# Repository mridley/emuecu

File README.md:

# emuecu
Emu ECU - An ECU for flightless birds

An ECU for UAV applications

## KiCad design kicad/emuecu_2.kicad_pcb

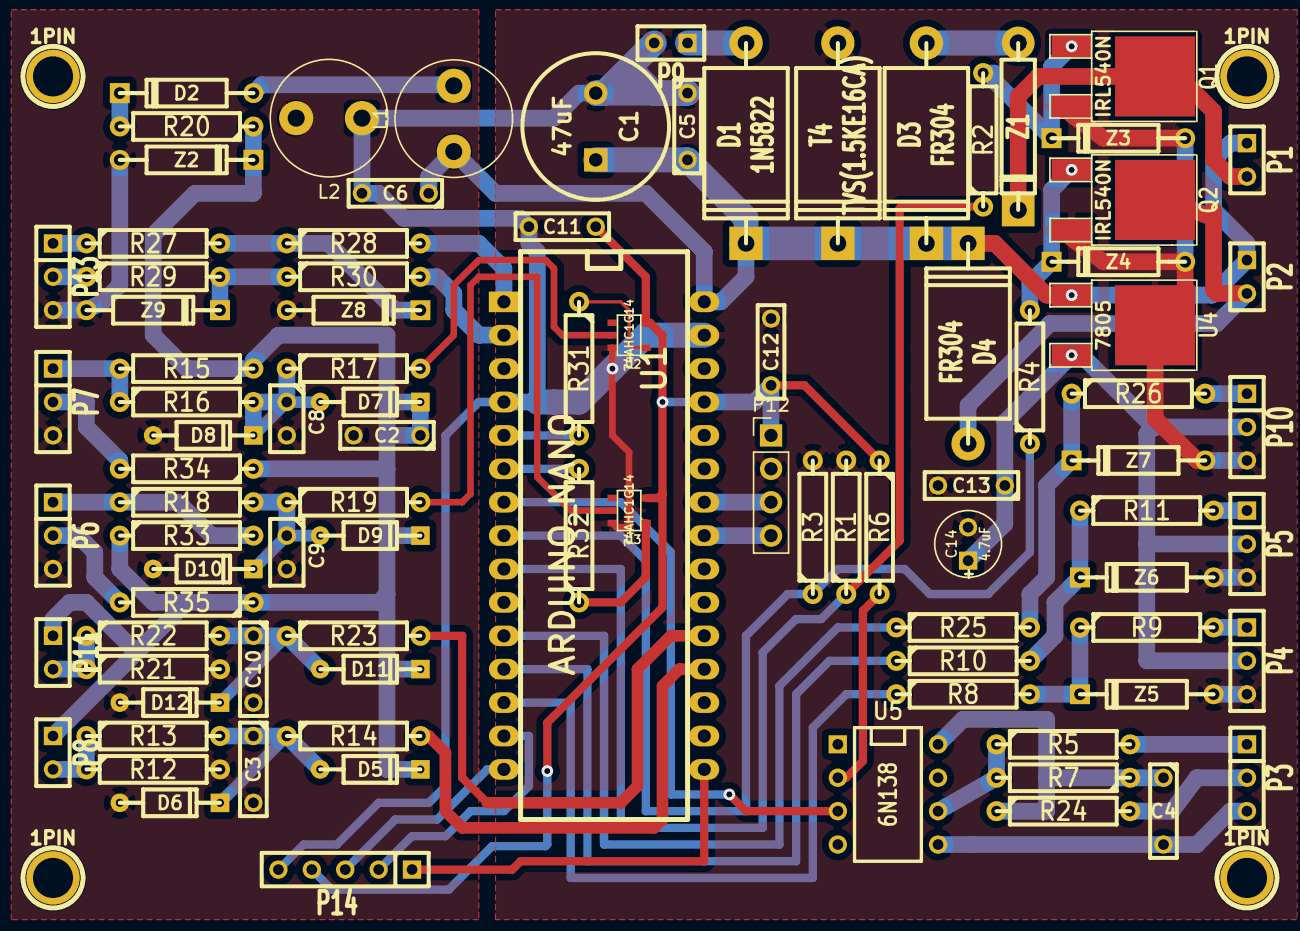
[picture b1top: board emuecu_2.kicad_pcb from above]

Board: 2 copper layers, 97 parts (0 on the bottom side), 61 nets.

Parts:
1PIN, 1PIN#2, 1PIN#3, 1PIN#4: P***; 1pin
C1: 47uF; C2V10
C2: 0.1 uF; C2
C3, C4, C5, C6, C10, C11, C12, C13: 0.1uF; C2
C8, C9: 10pF; C1
C14: 4.7uF; C1V5
D1: 1N5822; D6
D2: 1N4002; DO-41
D3, D4: FR304; D6
D5, D6, D7, D8, D9, D10, D11, D12: BAT48; DO-35
L1, L2: 47uH; L_Radial_D8.7mm_P5.00mm_Fastron_07HCP
P1: INJECTOR; SIL-2
P2: FAN/PUMP; SIL-2
P3: IGNITION; SIL-3
P4: LOAD; SIL-3
P5: THROTTLE; SIL-3
P6: SERVO; SIL-3
P7: HALL; SIL-3
P8: ENG TEMP; SIL-2
P9: POWER; SIL-2
P10: PUMP; SIL-3
P11: AIR TEMP; SIL-2
P12: I2C; PinHeader_1x04_P2.54mm_Vertical
P13: Serial; SIL-3
P14: SPI; SIL-5
Q1, Q2: IRL540N; DPAK2
R1, R3: 47k; R4
R2, R4, R14, R17, R19, R23, R30: 1k; R4
R5: 200; R4
R6: 330; R4
R7: 2.2k; R4
R8, R10, R25, R28, R31, R32: 180; R4
R9, R11, R26, R27: 470; R4
R12, R21: 22k; R4
R13, R15, R16, R18, R22, R29, R33: 10k; R4
R20: 240; R4
R24: 220; R4
R34, R35: 100; R4
T4: TVS(1.5KE16CA); D6
U1: ARDUINO_NANO; arduino_nano
U2, U3: 74AHC1G14; SOT23-5
U4: 7805; DPAK2
U5: 6N138; DIP-8__300
Z1: 1N5365B; D5
Z2: IN5919BG (5.6V); DO-41
Z3, Z4, Z5, Z6, Z7, Z8, Z9: 1N4733; DO-41

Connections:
+5C: C2.1, D5.2, D7.2, D9.2, D11.2, P8.1, P11.1, R15.1, R20.1, R33.1, R34.1, R35.1, Z2.2
+5V: C11.1, C12.1, P12.1, P14.4, R6.1, U1.27, U2.5, U3.5
+12V: C1.1, C5.1, C6.1, D1.2, D3.2, D4.2, L1.1, P1.1, P2.1, T4.2, U1.30, U4.1
GND: C1.2, C5.2, C6.2, C11.2, C12.2, C13.2, C14.2, L2.1, P4.3, P5.3, P9.2, P10.3, P12.2, P14.5, Q1.3, Q2.3, R1.2, R3.2, T4.1, U1.4, U1.29, U2.3, U3.3, U4.2, Z3.1, Z4.1, Z5.1, Z6.1, Z7.1
unnamed: C3.1, D5.1, D6.2, R13.2, R14.1
unnamed: C4.1, R7.1, R24.1, U5.8
unnamed: C4.2, P3.3, U5.5
unnamed: C8.1, D7.1, D8.2, R16.2, R17.1
unnamed: C9.1, D9.1, D10.2, R18.2, R19.1
unnamed: C10.1, D11.1, D12.2, R22.2, R23.1
unnamed: C13.1, C14.1, P4.2, P5.2, P10.2, U4.3
unnamed: D1.1, P9.1
unnamed: D2.1, L1.2
unnamed: D2.2, R20.2
unnamed: D3.1, Z1.1
unnamed: D4.1, P2.2, Q2.2
unnamed: P1.2, Q1.2, Z1.2
unnamed: P3.1, R5.2
unnamed: P3.2, R24.2
unnamed: P4.1, R9.2
unnamed: P5.1, R11.2
unnamed: P6.1, R18.1, R33.2
unnamed: P6.2, R35.2
unnamed: P7.1, R15.2, R16.1
unnamed: P7.2, R34.2
unnamed: P8.2, R12.1, R13.1
unnamed: P10.1, R26.2
unnamed: P11.2, R21.1, R22.1
unnamed: P12.3, U1.24
unnamed: P12.4, U1.23
unnamed: P13.1, R27.1
unnamed: P13.2, R29.1
unnamed: P14.1, U1.16
unnamed: P14.2, U1.14
unnamed: P14.3, U1.15
unnamed: Q1.1, R2.2, Z3.2
unnamed: Q2.1, R4.2, Z4.2
unnamed: R1.1, R2.1, U1.9
unnamed: R3.1, R4.1, U1.8
unnamed: R5.1, R7.2, U5.6
unnamed: R6.2, U5.2
unnamed: R8.1, U1.13
unnamed: R8.2, R9.1, Z5.2
unnamed: R10.1, U1.12
unnamed: R10.2, R11.1, Z6.2
unnamed: R14.2, U1.19
unnamed: R17.2, U2.2
unnamed: R19.2, U3.2
unnamed: R23.2, U1.20
unnamed: R25.1, U1.11
unnamed: R25.2, R26.1, Z7.2
unnamed: R27.2, R28.1, Z8.2
unnamed: R28.2, U1.1
unnamed: R29.2, R30.1, Z9.2
unnamed: R30.2, U1.2
unnamed: R31.1, U2.4
unnamed: R31.2, U1.5
unnamed: R32.1, U3.4
unnamed: R32.2, U1.6
unnamed: U1.7, U5.3
SGND: C2.2, C3.2, C8.2, C9.2, C10.2, D6.1, D8.1, D10.1, D12.1, L2.2, P6.3, P7.3, P13.3, R12.2, R21.2, Z2.1, Z8.1, Z9.1

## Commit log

2015-08-28 Adding pin allocation doc
2015-08-28 Add schematics
2015-08-28 Add initial scraps of src
2015-10-31 second iteration
2015-10-31 breaking it down. modify timers.
2015-11-02 fixing bugs in timer0 overflow and analogue input
2015-11-03 Fixing some port config bugs
2015-11-06 Fixing up pwm input. reorganise some inputs to use OC0x for mosfet outputs.
2015-11-07 Commiting the code used for firt successful test run!
2015-11-22 updates to schematic/pcb
2015-11-22 changes for inverter on inputs
2015-12-02 Changes for table lookup of rpm and basic fuel injection map
2016-01-07 updates to schematic, minor changes to map
2018-10-04 bme280 support. update resistors for thermister in schematic.
2018-10-07 adding egt thermocouple
2018-10-10 eeprom config
2018-10-18 bigger map, compute default map, fix humidity
2018-10-20 status and analogue temp calibration tables
2018-10-21 state machine, auto start. pt compensation
2018-10-24 uart interrupts
2018-10-26 json output, thr input config. auto start.
2018-10-27 fix json output. add pytuner.py for basic monitoring.
2019-10-28 added: kill on zero throttle. added: basic cht temp and crank enrichment. small amount of fudge
2019-11-01 refactor and log max 6675 errors
2019-11-03 changed injection max duration. some refactoring
2019-11-10 fix bug in over temp enrichment. Added Start throttle control
2019-11-24 switch to 5Hz telemetry
2019-11-30 added -Werror
2019-11-30 added command processing
    supports:
    - dump config
    - change telem period
    - set or show config variables
2019-11-30 added easier dumping of tables
2019-11-30 allow environemnt override of AVRDUDE_PORT
2019-11-30 added "config defaults"
2019-12-08 support reverse servo
2019-12-08 change to json output for set/show vars
2019-12-14 allow for json formatted get/set
2019-12-15 config restore at boot.
2019-12-15 fixed default period
2019-12-15 added thr_over settable value
    allows for software throttle from flight controller
2019-12-15 fix inj_ticks status, wasn't being updated and now uint16_t
2019-12-15 fix backwards DO-35 after kicad upgrade
2019-12-27 throttle arming and fixes to default map
2019-12-28 added software throttle support
2019-12-28 aded injector add/multi factors
